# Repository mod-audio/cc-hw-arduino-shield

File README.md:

control-chain-arduino-shield
============================

This repository contains the schematics and PCB design files for Control Chain Arduino Shield hardware. It serves as a way for people to create new peripheral to be used in conjunction with MOD (http://moddevices.com/) via its Control Chain interface.

These files were created and can be improved with KiCAD, a free software Electronics CAD which is available at http://www.kicad.org/

## Check out instructions ##

This project uses a set of KiCAD symbols and footprints provided by the official KiCad library (https://github.com/KiCad/). In order to properly fetch these dependencies, which are configured as submodule repositories, you have to use the **--recursive** attribute in the following **git** command:

> git clone --recursive https://github.com/portalmod/control-chain-arduino-shield.git

## Licensing ##

This is an Open Hardware project and all of the files in this repository are licensed under the terms of the "Creative Commons By-SA" license.

## Sample Code / Arduino Library ##

There is an Arduino library for making it easy to develop your own Control Chain peripherals freely available at https://github.com/portalmod/control-chain-arduino-lib

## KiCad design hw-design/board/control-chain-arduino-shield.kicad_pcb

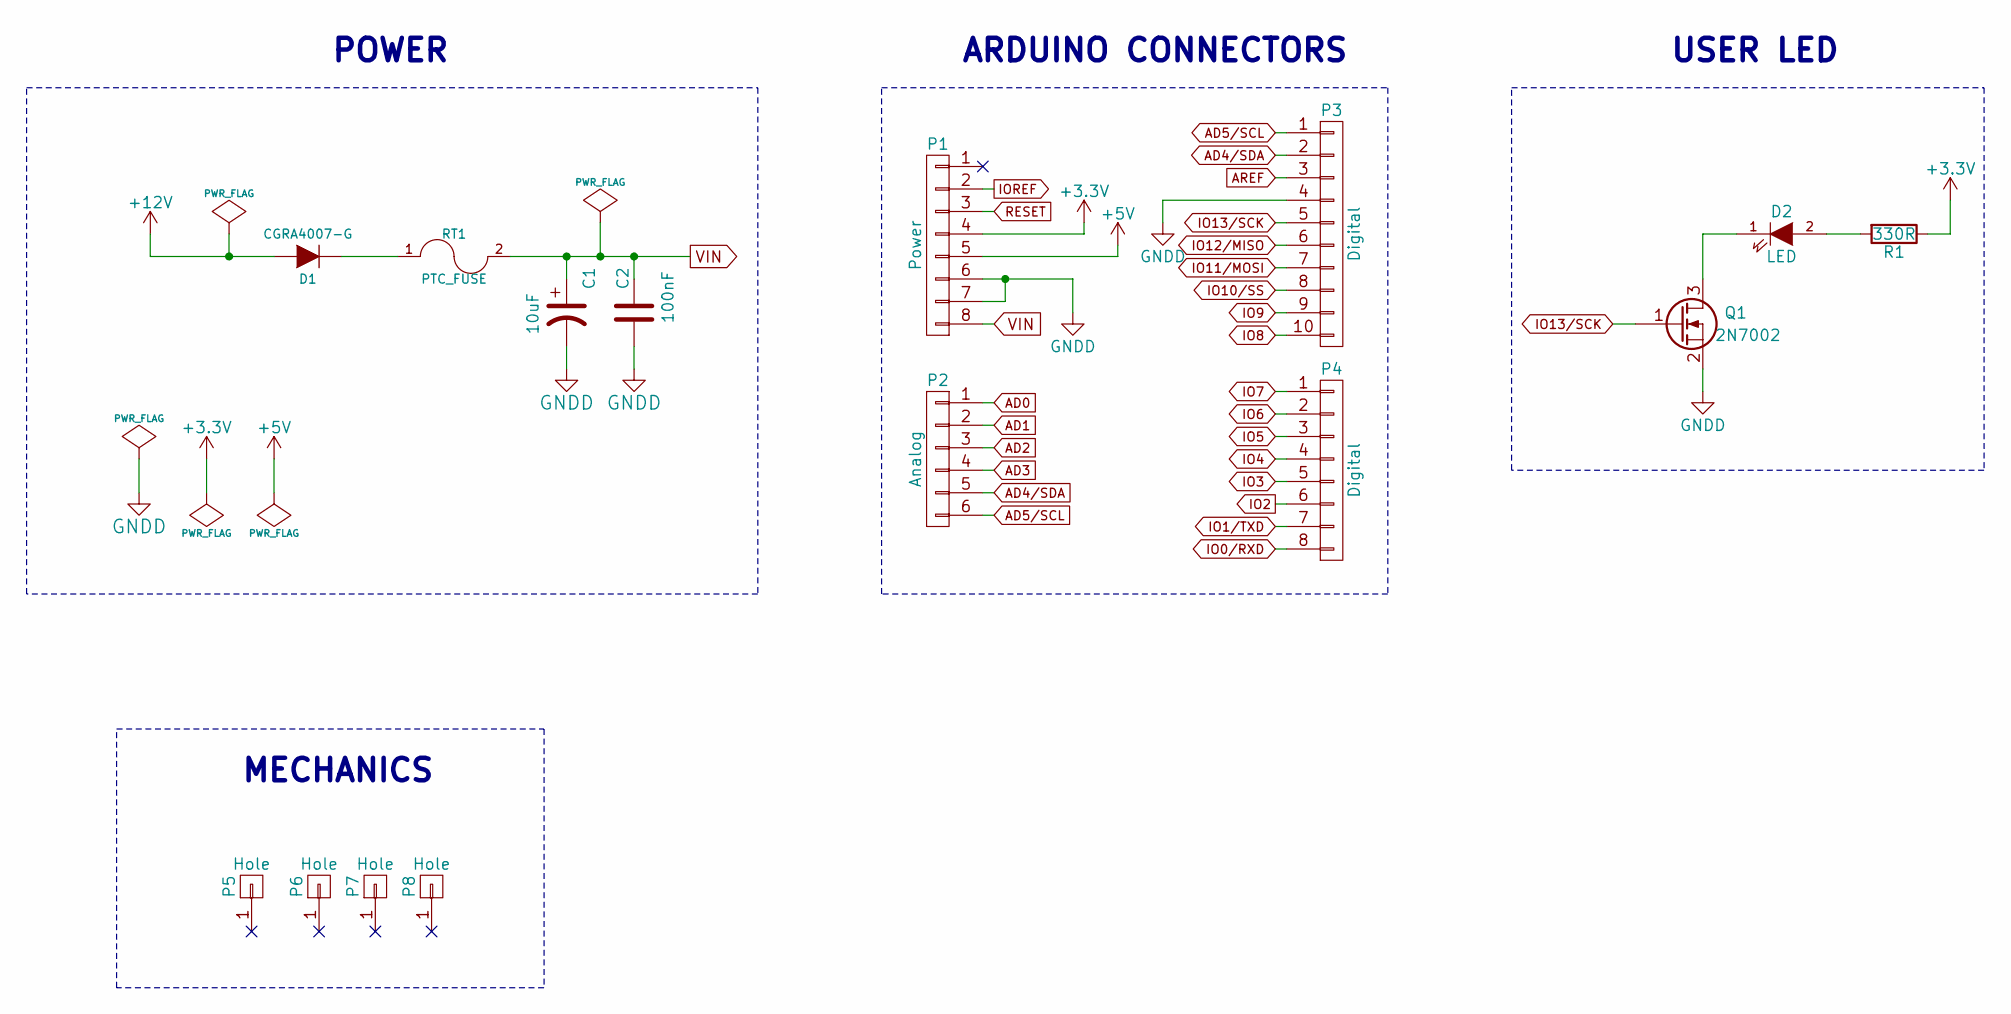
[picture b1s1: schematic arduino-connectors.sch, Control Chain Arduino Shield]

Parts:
C1: 10uF; c_elec_5x5.3; MPN UWX1E100MCL1GB
C2: 100nF; C_0603; MPN C1608X7R1E104K080AA
D1: CGRA4007-G; Diode-SMA_Standard; MPN CGRA4007-G
D2: LED; LED-0603; MPN LS Q976-NR-1
P1: Power; Socket_Strip_Arduino_1x08; MPN PREC008SFAN-RC
P2: Analog; Socket_Strip_Arduino_1x06; MPN PREC006SFAN-RC
P3: Digital; Socket_Strip_Arduino_1x10; MPN PREC010SFAN-RC
P4: Digital; Socket_Strip_Arduino_1x08; MPN PREC008SFAN-RC
P5, P6, P7, P8: Hole; Arduino_1pin
Q1: 2N7002; SOT-23; MPN 2N7002P,215
R1: 330R; R_0603; MPN RMCF0603JT330R
RT1: PTC_FUSE; R_1210; MPN 0ZCB0050FF2G

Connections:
+3V3: P1.4, R1.1; also elsewhere on the board
+5V: P1.5; also elsewhere on the board
+12V: D1.2 (A); also elsewhere on the board
AD0: P2.1; also elsewhere on the board
AD1: P2.2; also elsewhere on the board
AD2: P2.3; also elsewhere on the board
AD3: P2.4; also elsewhere on the board
AD4/SDA: P2.5, P3.2; also elsewhere on the board
AD5/SCL: P2.6, P3.1; also elsewhere on the board
AREF: P3.3; also elsewhere on the board
GNDD: C1.2, C2.2, P1.6, P1.7, P3.4, Q1.2 (S); also elsewhere on the board
IO0/RXD: P4.8; also elsewhere on the board
IO1/TXD: P4.7; also elsewhere on the board
IO2: P4.6; also elsewhere on the board
IO3: P4.5; also elsewhere on the board
IO4: P4.4; also elsewhere on the board
IO5: P4.3; also elsewhere on the board
IO6: P4.2; also elsewhere on the board
IO7: P4.1; also elsewhere on the board
IO8: P3.10; also elsewhere on the board
IO9: P3.9; also elsewhere on the board
IO10/SS: P3.8; also elsewhere on the board
IO11/MOSI: P3.7; also elsewhere on the board
IO12/MISO: P3.6; also elsewhere on the board
IO13/SCK: P3.5, Q1.1 (G); also elsewhere on the board
IOREF: P1.2; also elsewhere on the board
unnamed: D1.1 (K), RT1.1
unnamed: D2.1 (K), Q1.3 (D)
unnamed: D2.2 (A), R1.2
RESET: P1.3; also elsewhere on the board
VIN: C1.1, C2.1, P1.8, RT1.2; also elsewhere on the board

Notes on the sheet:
POWER
ARDUINO CONNECTORS
USER LED
MECHANICS

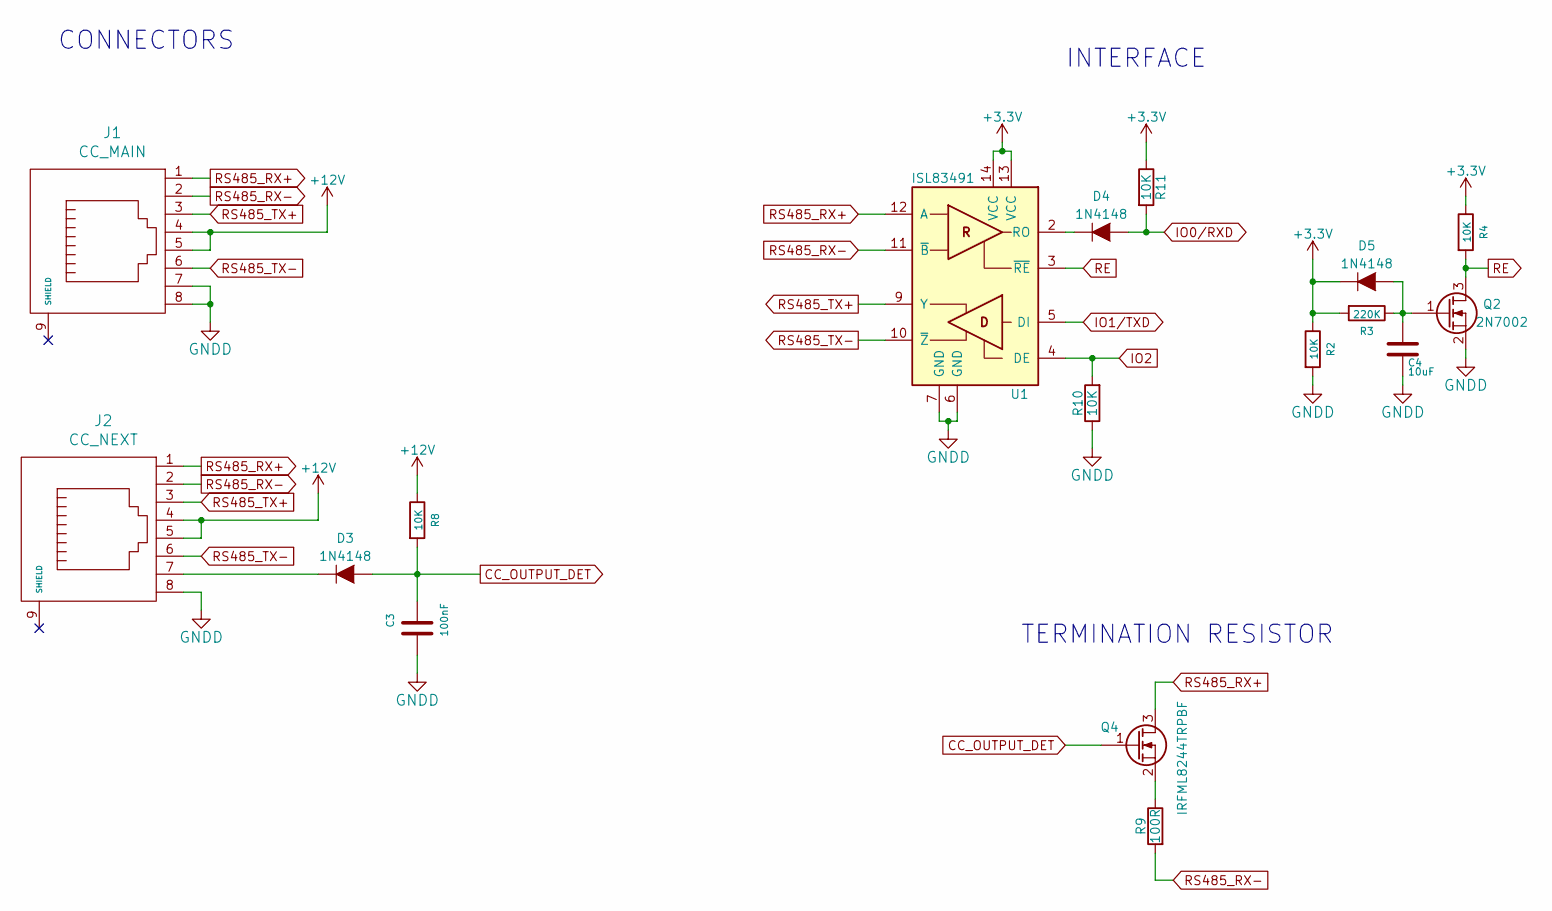
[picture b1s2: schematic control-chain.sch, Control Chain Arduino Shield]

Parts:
C3: 100nF; C_0603; MPN C1608X7R1E104K080AA
C4: 10uF; C_0603; MPN GRM188R60G106ME47D
D3, D4, D5: 1N4148; SOD-323; MPN 1N4148WX-TP
J1: CC_MAIN; 54602-908LF; MPN 54602-908LF
J2: CC_NEXT; 54602-908LF; MPN 54602-908LF
Q2: 2N7002; SOT-23; MPN 2N7002P,215
Q4: IRFML8244TRPBF; SOT-23; MPN IRFML8244TRPBF
R2, R4, R8, R10, R11: 10K; R_0603; MPN RMCF0603JT10K0
R3: 220K; R_0603; MPN RMCF0603JT220K
R9: 100R; R_0805; MPN ERJ-P06F1000V
U1: ISL83491; SOIC-14_3.9x8.7mm_Pitch1.27mm; MPN ISL83491IBZ

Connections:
+3V3: D5.1 (K), R2.1, R3.2, R4.1, R11.1, U1.13 (VCC), U1.14 (VCC); also elsewhere on the board
+12V: J1.4, J1.5, J2.4, J2.5, R8.1; also elsewhere on the board
CC_OUTPUT_DET: C3.1, D3.2 (A), Q4.1 (G), R8.2
GNDD: C3.2, C4.2, J1.7, J1.8, J2.8, Q2.2 (S), R2.2, R10.1, U1.6 (GND), U1.7 (GND); also elsewhere on the board
IO0/RXD: D4.2 (A), R11.2; also elsewhere on the board
IO1/TXD: U1.5 (DI); also elsewhere on the board
IO2: R10.2, U1.4 (DE); also elsewhere on the board
unnamed: C4.1, D5.2 (A), Q2.1 (G), R3.1
unnamed: D3.1 (K), J2.7
unnamed: D4.1 (K), U1.2 (RO)
unnamed: Q4.2 (S), R9.1
RE: Q2.3 (D), R4.2, U1.3 (~RE)
RS485_RX+: J1.1, J2.1, Q4.3 (D), U1.12 (A)
RS485_RX-: J1.2, J2.2, R9.2, U1.11 (~B)
RS485_TX+: J1.3, J2.3, U1.9 (Y)
RS485_TX-: J1.6, J2.6, U1.10 (~Z~)

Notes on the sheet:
TERMINATION RESISTOR
CONNECTORS
INTERFACE

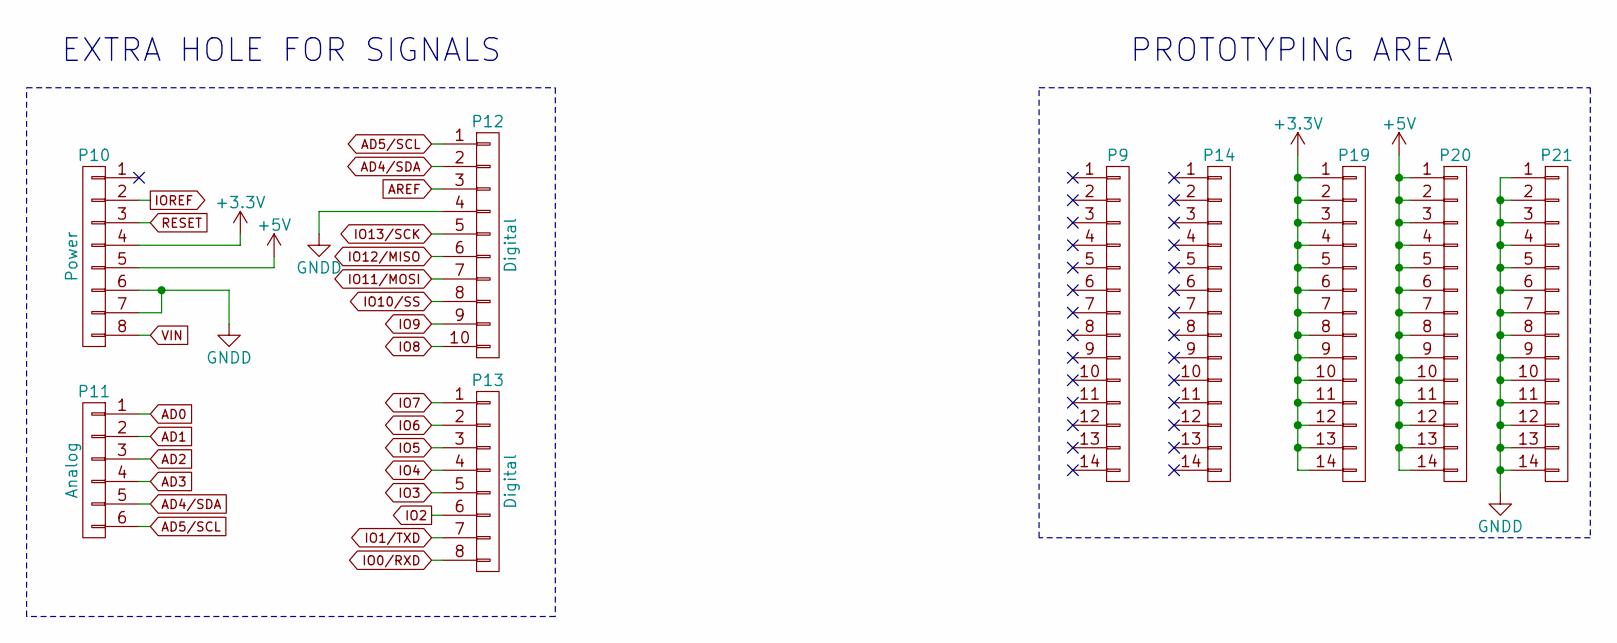
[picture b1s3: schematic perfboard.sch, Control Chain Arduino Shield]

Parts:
P9, P14: Perfboard
P10: Power; Socket_Strip_Arduino_1x08
P11: Analog; Socket_Strip_Arduino_1x06
P12: Digital; Socket_Strip_Arduino_1x10
P13: Digital; Socket_Strip_Arduino_1x08
P19, P20, P21: Pin_Header_Straight_1x14

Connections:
+3V3: P10.4, P19.1, P19.2, P19.3, P19.4, P19.5, P19.6, P19.7, P19.8, P19.9, P19.10, P19.11, P19.12, P19.13, P19.14; also elsewhere on the board
+5V: P10.5, P20.1, P20.2, P20.3, P20.4, P20.5, P20.6, P20.7, P20.8, P20.9, P20.10, P20.11, P20.12, P20.13, P20.14; also elsewhere on the board
AD0: P11.1; also elsewhere on the board
AD1: P11.2; also elsewhere on the board
AD2: P11.3; also elsewhere on the board
AD3: P11.4; also elsewhere on the board
AD4/SDA: P11.5, P12.2; also elsewhere on the board
AD5/SCL: P11.6, P12.1; also elsewhere on the board
AREF: P12.3; also elsewhere on the board
GNDD: P10.6, P10.7, P12.4, P21.1, P21.2, P21.3, P21.4, P21.5, P21.6, P21.7, P21.8, P21.9, P21.10, P21.11, P21.12, P21.13, P21.14; also elsewhere on the board
IO0/RXD: P13.8; also elsewhere on the board
IO1/TXD: P13.7; also elsewhere on the board
IO2: P13.6; also elsewhere on the board
IO3: P13.5; also elsewhere on the board
IO4: P13.4; also elsewhere on the board
IO5: P13.3; also elsewhere on the board
IO6: P13.2; also elsewhere on the board
IO7: P13.1; also elsewhere on the board
IO8: P12.10; also elsewhere on the board
IO9: P12.9; also elsewhere on the board
IO10/SS: P12.8; also elsewhere on the board
IO11/MOSI: P12.7; also elsewhere on the board
IO12/MISO: P12.6; also elsewhere on the board
IO13/SCK: P12.5; also elsewhere on the board
IOREF: P10.2; also elsewhere on the board
RESET: P10.3; also elsewhere on the board
VIN: P10.8; also elsewhere on the board

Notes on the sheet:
EXTRA HOLE FOR SIGNALS
PROTOTYPING AREA

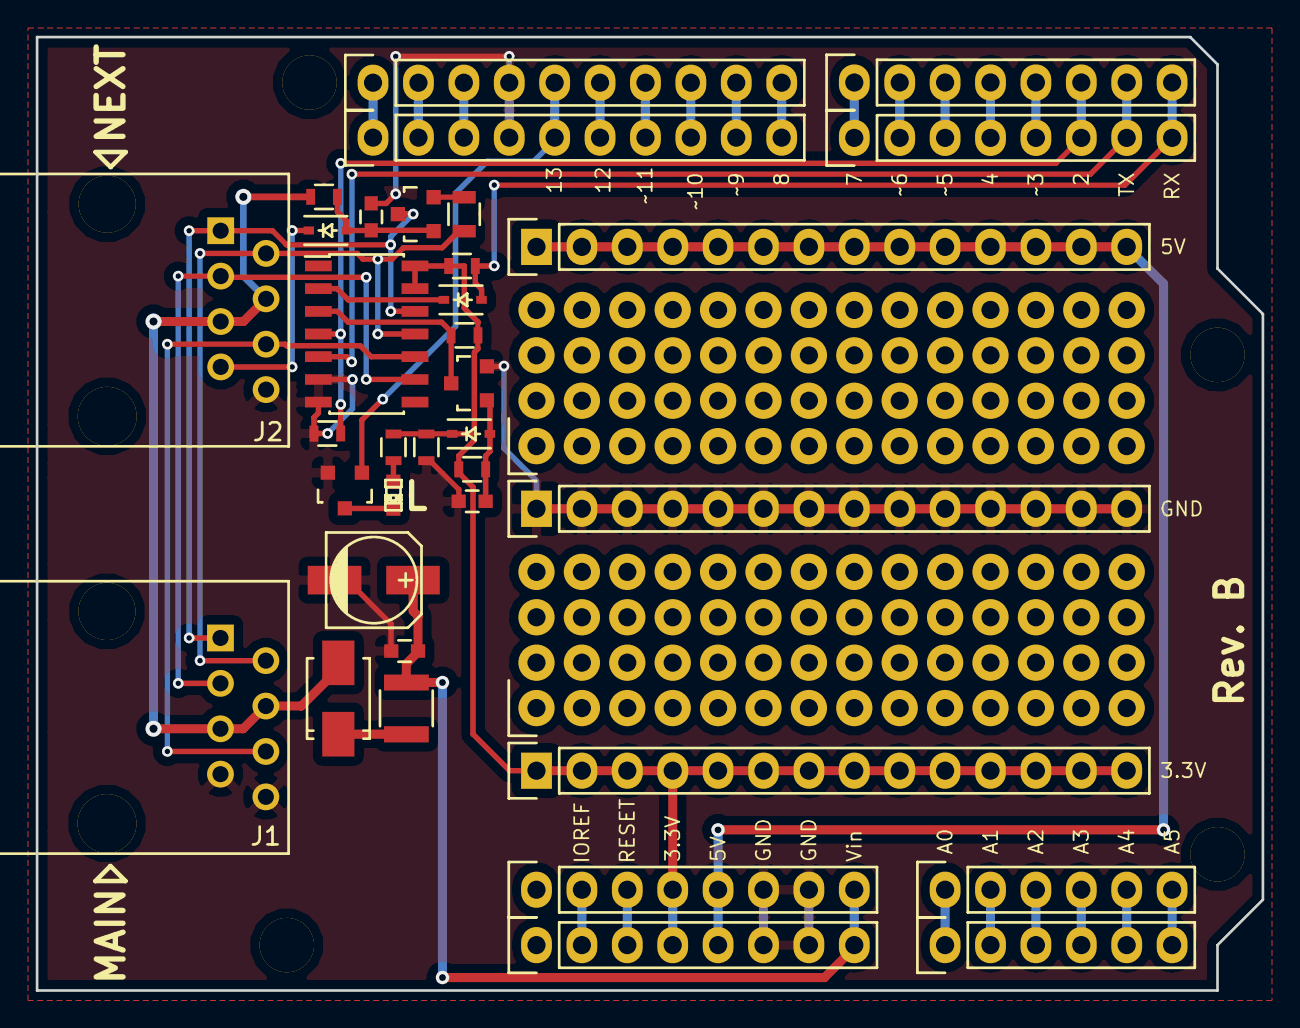
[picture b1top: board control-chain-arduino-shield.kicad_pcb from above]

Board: 2 copper layers, 68.6 x 53.3 mm, 41 parts (0 on the bottom side), 41 nets.

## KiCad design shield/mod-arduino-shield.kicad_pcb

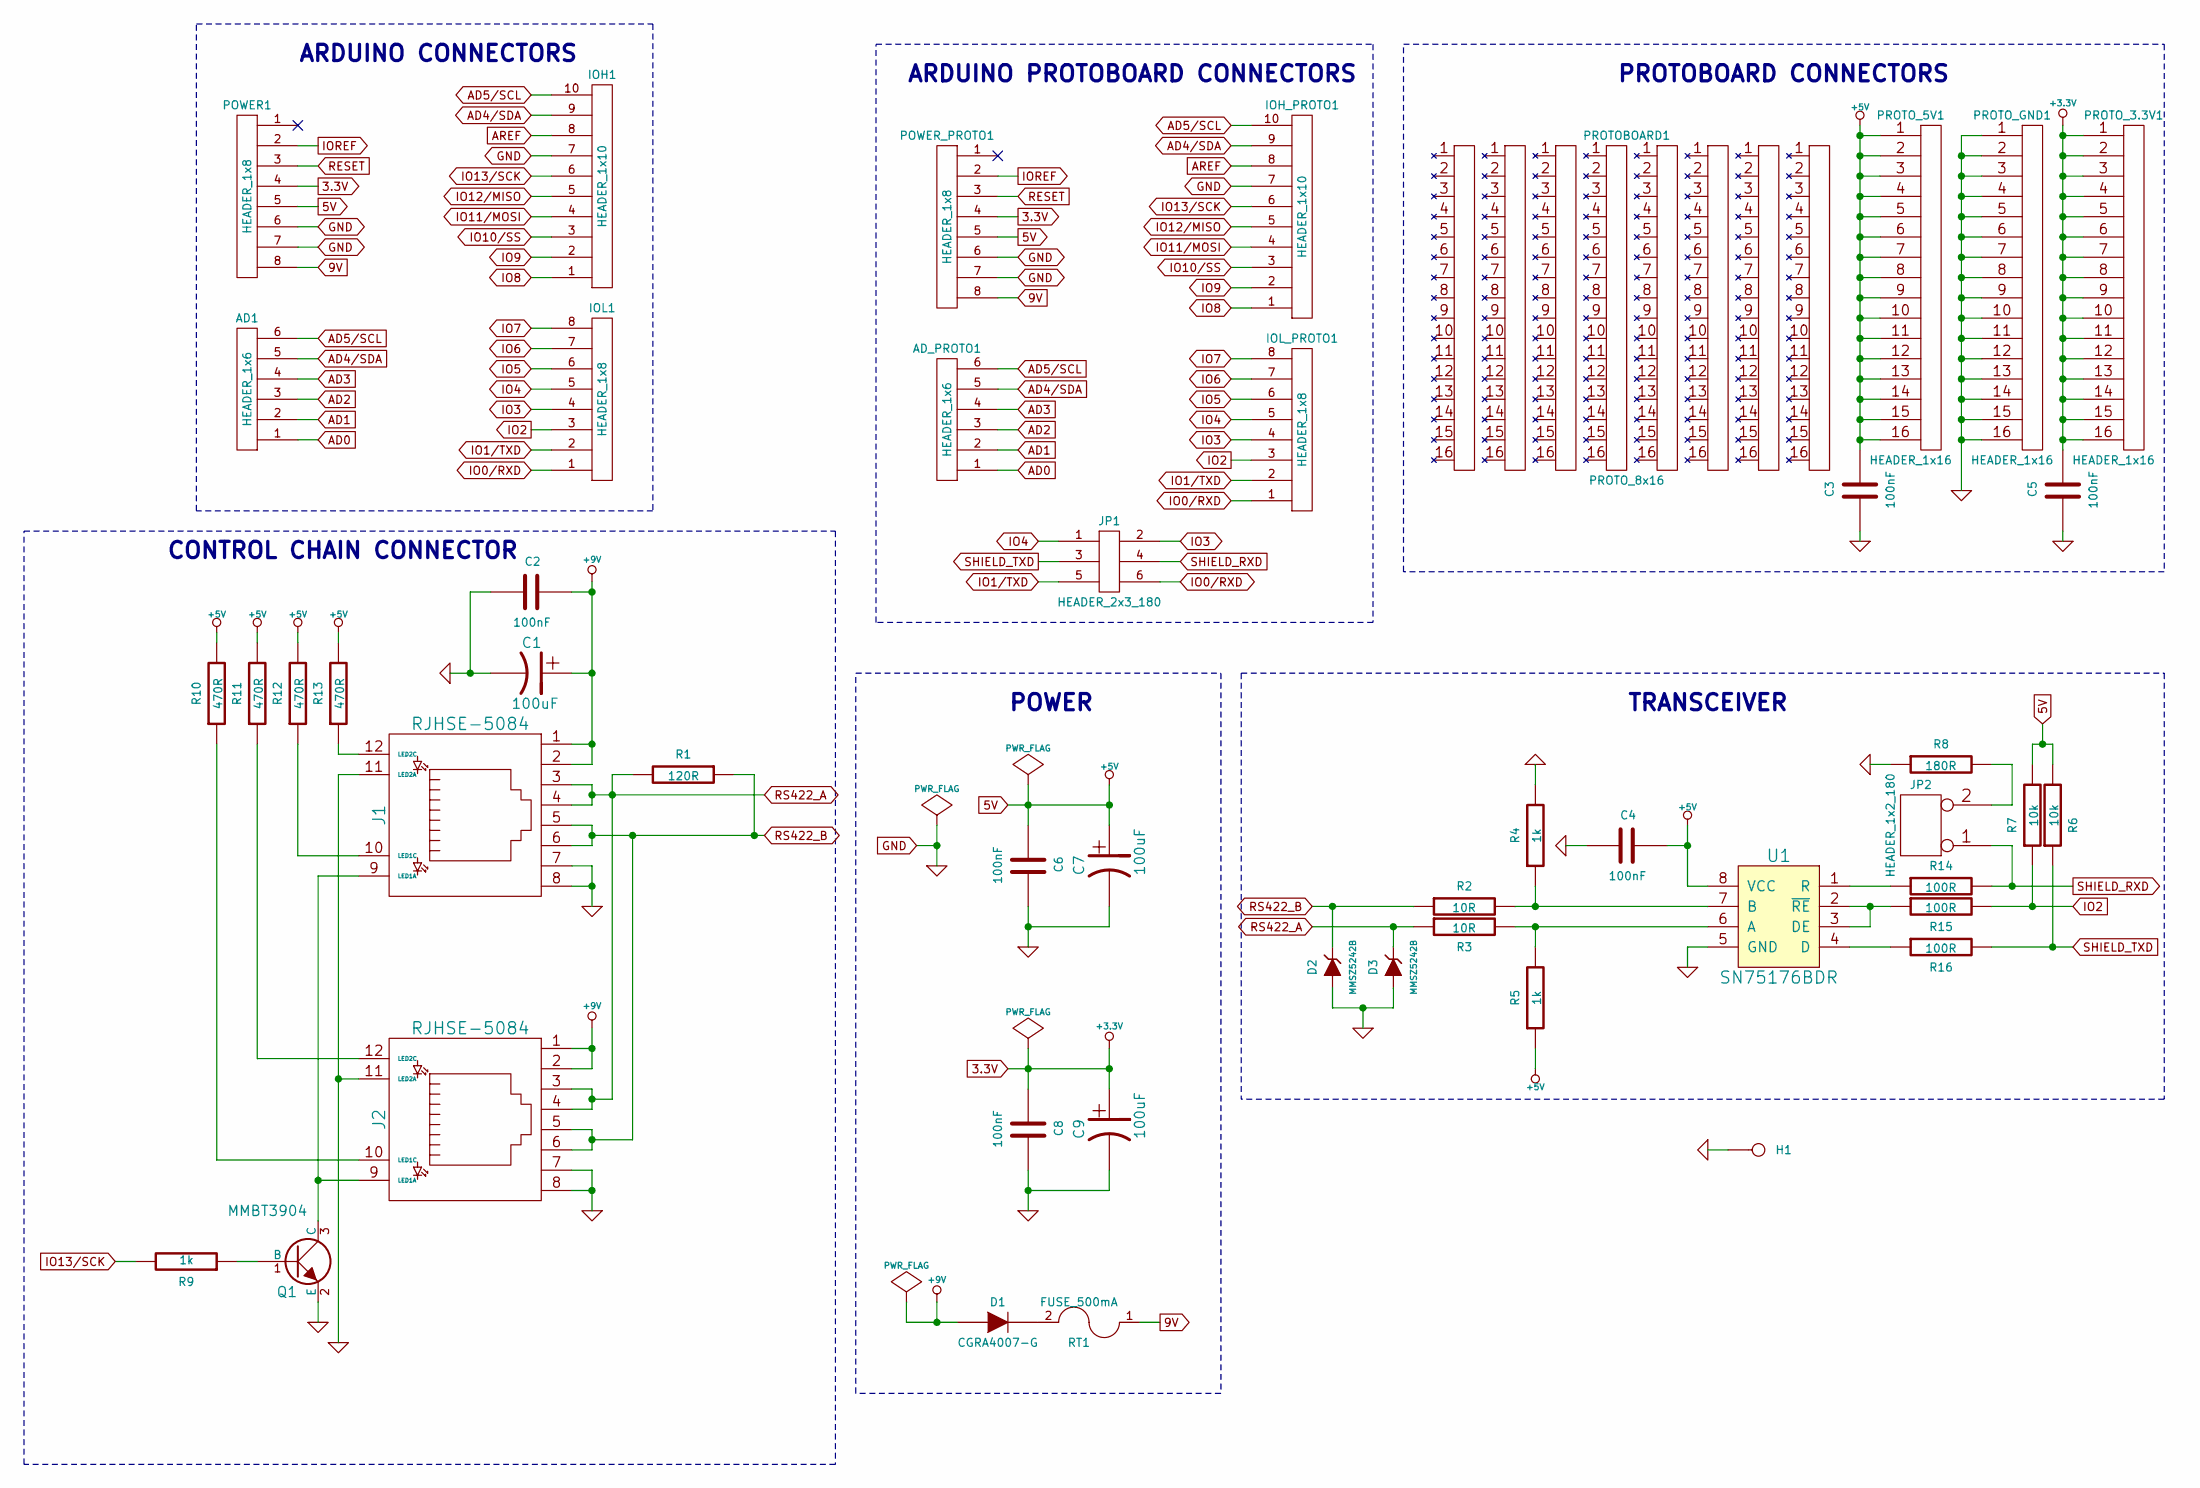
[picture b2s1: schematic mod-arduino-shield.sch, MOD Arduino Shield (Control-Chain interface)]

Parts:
AD1: HEADER_1x6; HEADER_100MIL_1R6P_PTH
AD_PROTO1: HEADER_1x6; HEADER_100MIL_1R6P_PTH
C1, C7, C9: 100uF; CAP_RAD_5MM
C2, C3, C4, C5, C6, C8: 100nF; SM0805
D1: CGRA4007-G; DO-214AC(SMA)
D2, D3: MMSZ5242B; SOD123
H1: HOLE; HOLE_3MM
IOH1: HEADER_1x10; HEADER_100MIL_1R10P_PTH
IOH_PROTO1: HEADER_1x10; HEADER_100MIL_1R10P_PTH
IOL1: HEADER_1x8; HEADER_100MIL_1R8P_PTH
IOL_PROTO1: HEADER_1x8; HEADER_100MIL_1R8P_PTH
J1, J2: RJHSE-5084; RJ45-RJHSE5084
JP1: HEADER_2x3_180; HEADER_100MIL_2R3P_PTH
JP2: HEADER_1x2_180; HEADER_100MIL_1R2P_PTH
POWER1: HEADER_1x8; HEADER_100MIL_1R8P_PTH
POWER_PROTO1: HEADER_1x8; HEADER_100MIL_1R8P_PTH
PROTOBOARD1: PROTO_8x16; PROTOBOARD_100MIL_8R16P_PTH
PROTO_3.3V1, PROTO_5V1: HEADER_1x16; PROTOBOARD_100MIL_1R16P_PTH
PROTO_GND1: HEADER_1x16; PROTOBOARD_100MIL_1R16P_PTH
Q1: MMBT3904; SOT23
R1: 120R; SM0805
R2, R3: 10R; SM0805
R4, R5, R9: 1k; SM0805
R6, R7: 10k; SM0805
R8: 180R; SM0805
R10, R11, R12, R13: 470R; SM0805
R14, R15, R16: 100R; SM0805
RT1: FUSE_500mA; SM1210
U1: SN75176BDR; SO8E

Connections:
3.3V: C5.2, C8.2, C9.1, POWER1.4, POWER_PROTO1.4, PROTO_3.3V1.1, PROTO_3.3V1.2, PROTO_3.3V1.3, PROTO_3.3V1.4, PROTO_3.3V1.5, PROTO_3.3V1.6, PROTO_3.3V1.7, PROTO_3.3V1.8, PROTO_3.3V1.9, PROTO_3.3V1.10, PROTO_3.3V1.11, PROTO_3.3V1.12, PROTO_3.3V1.13, PROTO_3.3V1.14, PROTO_3.3V1.15, PROTO_3.3V1.16
5V: C3.2, C4.2, C6.2, C7.1, POWER1.5, POWER_PROTO1.5, PROTO_5V1.1, PROTO_5V1.2, PROTO_5V1.3, PROTO_5V1.4, PROTO_5V1.5, PROTO_5V1.6, PROTO_5V1.7, PROTO_5V1.8, PROTO_5V1.9, PROTO_5V1.10, PROTO_5V1.11, PROTO_5V1.12, PROTO_5V1.13, PROTO_5V1.14, PROTO_5V1.15, PROTO_5V1.16, R5.1, R6.2, R7.2, R10.2, R11.2, R12.2, R13.2, U1.8 (VCC)
9V: POWER1.8, POWER_PROTO1.8, RT1.1
+9V: C1.1, C2.2, D1.1 (A), J1.1, J1.2, J2.1, J2.2
AD0: AD1.1, AD_PROTO1.1
AD1: AD1.2, AD_PROTO1.2
AD2: AD1.3, AD_PROTO1.3
AD3: AD1.4, AD_PROTO1.4
AD4/SDA: AD1.5, AD_PROTO1.5, IOH1.9, IOH_PROTO1.9
AD5/SCL: AD1.6, AD_PROTO1.6, IOH1.10, IOH_PROTO1.10
AREF: IOH1.8, IOH_PROTO1.8
GND: C1.2, C2.1, C3.1, C4.1, C5.1, C6.1, C7.2, C8.1, C9.2, D2.1 (A), D3.1 (A), H1.1, IOH1.7, IOH_PROTO1.7, J1.7, J1.8, J1.11 (LED2A), J2.7, J2.8, J2.11 (LED2A), POWER1.6, POWER1.7, POWER_PROTO1.6, POWER_PROTO1.7, PROTO_GND1.1, PROTO_GND1.2, PROTO_GND1.3, PROTO_GND1.4, PROTO_GND1.5, PROTO_GND1.6, PROTO_GND1.7, PROTO_GND1.8, PROTO_GND1.9, PROTO_GND1.10, PROTO_GND1.11, PROTO_GND1.12, PROTO_GND1.13, PROTO_GND1.14, PROTO_GND1.15, PROTO_GND1.16, Q1.2 (E), R4.2, R8.1, U1.5 (GND)
IO0/RXD: IOL1.1, IOL_PROTO1.1, JP1.6
IO1/TXD: IOL1.2, IOL_PROTO1.2, JP1.5
IO2: IOL1.3, IOL_PROTO1.3, R7.1, R15.2
IO3: IOL1.4, IOL_PROTO1.4, JP1.2 (P1)
IO4: IOL1.5, IOL_PROTO1.5, JP1.1
IO5: IOL1.6, IOL_PROTO1.6
IO6: IOL1.7, IOL_PROTO1.7
IO7: IOL1.8, IOL_PROTO1.8
IO8: IOH1.1, IOH_PROTO1.1
IO9: IOH1.2, IOH_PROTO1.2
IO10/SS: IOH1.3, IOH_PROTO1.3
IO11/MOSI: IOH1.4, IOH_PROTO1.4
IO12/MISO: IOH1.5, IOH_PROTO1.5
IO13/SCK: IOH1.6, IOH_PROTO1.6, R9.2
IOREF: POWER1.2, POWER_PROTO1.2
unnamed: D1.2 (K), RT1.2
unnamed: J1.9 (LED1A), J2.9 (LED1A), Q1.3 (C)
unnamed: J1.10 (LED1C), R12.1
unnamed: J1.12 (LED2C), R13.1
unnamed: J2.10 (LED1C), R10.1
unnamed: J2.12 (LED2C), R11.1
unnamed: JP2.2 (PM), R8.2
unnamed: Q1.1 (B), R9.1
unnamed: R2.2, R4.1, U1.7 (B)
unnamed: R3.2, R5.2, U1.6 (A)
unnamed: R14.1, U1.1 (R)
unnamed: R15.1, U1.2 (~RE), U1.3 (DE)
unnamed: R16.1, U1.4 (D)
RESET: POWER1.3, POWER_PROTO1.3
RS422_A: D3.2 (K), J1.3, J1.4, J2.3, J2.4, R1.2, R3.1
RS422_B: D2.2 (K), J1.5, J1.6, J2.5, J2.6, R1.1, R2.1
SHIELD_RXD: JP1.4 (P2), JP2.1, R14.2
SHIELD_TXD: JP1.3 (P2), R6.1, R16.2

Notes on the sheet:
CONTROL CHAIN CONNECTOR
ARDUINO CONNECTORS
ARDUINO PROTOBOARD CONNECTORS
PROTOBOARD CONNECTORS
TRANSCEIVER
POWER

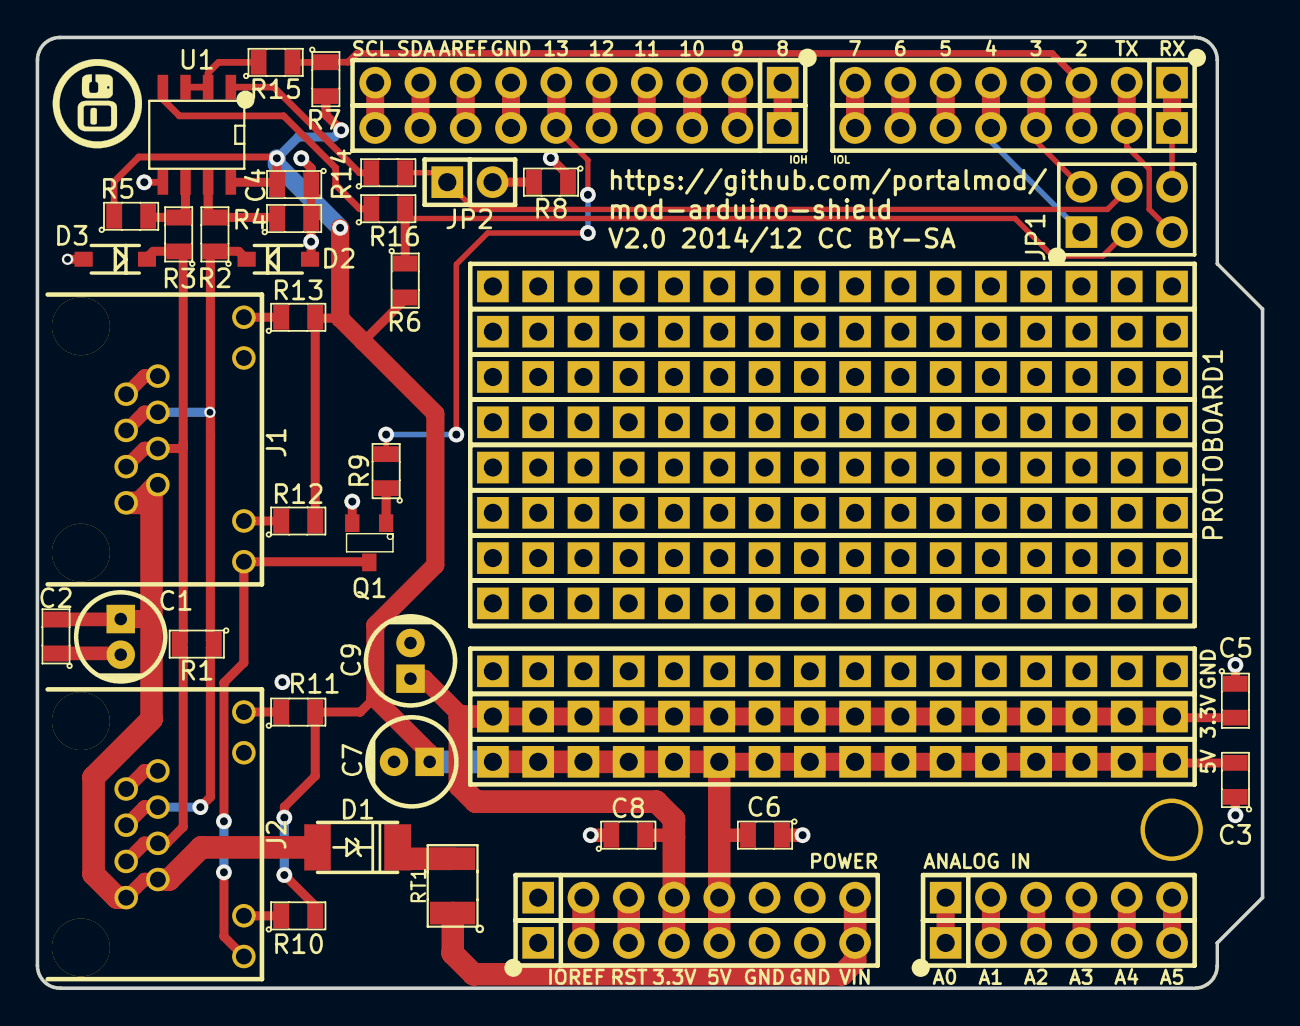
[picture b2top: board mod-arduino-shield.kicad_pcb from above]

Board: 2 copper layers, 68.7 x 53.3 mm, 49 parts (0 on the bottom side), 45 nets.

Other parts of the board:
LOGO: LOGO; MOD_Logo_Small

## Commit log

2014-09-16 Initial commit for MOD Arduino Shield. Shield for interfacing the Arduino to the Control Chain of MOD. Opening the hardware for the community.
2014-12-01 Improving README.md and declaring the copyright license for this repository.
2014-12-02 Adding a few footprints exported from the footswitch repository that were using the old library file format (.mod).
2014-12-02 replacing specific references and values in the footprints by generic ones
2014-12-04 Fixing typo in the .gitignore filename and actually deleting the files it should be ignoring.
2014-12-04 Adding metadata to the schematics of the example circuits.
2014-12-04 removing local copy of footprints and adding the mod-kicad-footprints repository as a submodule dependency
2014-12-04 updating component => footprint mapping file to use the new footprint library
2014-12-04 improving the README and pointing users to the repository containing sample code and the arduino library (fix issue #5)
2014-12-04 add metadata and licensing info to the schematics file (fix issue #4)
2014-12-09 fix issue #3: Add "CC by-SA" license logo to the PCB silk layer Added MOD logo and improved/rearranged previous silk text.
2014-12-09 fix issue #6: use same labels on shield as used in arduino
2014-12-09 fix issue #2: rename VCCIO to IOREF
2014-12-09 fix issue #1: IOREF should not be used to power the circuit
2014-12-18 plotting the schematics to PDF files to be kept in the /docs directories (we should always update these PDF files when we make changes to the schematics).
2015-06-25 README updated
2015-06-25 added hw-design directory
2015-06-25 sch: setting up footprints
2015-06-26 adding footprint to local project directory (submodule)
2015-06-26 BOM generated
2015-06-26 importing arduino uno layout template
2015-06-26 sch: fixing footprints and renaming some connectors
2015-06-26 pcb: importing netlist
2015-06-26 pcb: RJ45 connectors placed
2015-06-26 sch: adjusting perfboard
2015-06-26 pcb: initial placement of components
2015-06-26 pcb: setting design rules
2015-06-26 pcb: design almost done, missing 2 or 3 tracks
2015-06-29 sch: fixing connectors I/Os pinout
2015-06-29 pcb: all tracks done + silkscreen of I/Os
2015-06-29 pcb: adjusting holes
2015-06-29 BOM updated
2015-06-29 removing old stuff
2015-09-29 sch: changing input voltage from +9V to +12V
2015-10-15 sch: fixing MOSFET + new BOM exported
2015-10-15 pcb: updating layout
2015-10-17 adding board size
2015-10-17 improving silkscreen
2015-10-17 panel created
2015-10-17 fixing user led voltage
2016-06-08 fix RJ45 pinout
2016-06-08 fix all DRC issues
2016-06-08 add perfboard footprint
2016-06-08 replace multiple headers by perfboard
2016-06-08 fix pin name (vin)
2016-06-08 new netlist
2016-06-09 connect all voltage inputs pins
2016-06-09 update layout to last schematic
2016-06-17 change RJ45 connector
2016-06-17 add header MPN to BOM
2016-06-17 add local footprint library
2016-07-12 remove panel gerber files
2016-07-12 update BOM
2016-07-12 export gerber
2016-07-12 remove panel project files
2017-04-26 generate schematic pdf
2018-05-18 add enable circuit for RE pin
2018-05-18 update footprints (remove silkscreen from pads)
2018-05-18 move led position
2018-05-18 update gerber and pdf files
2021-11-10 Update README.md
    https://forum.kicad.info/t/warning-avoid-all-links-to-kicad-pcb-org-use-kicad-org/31521

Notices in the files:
shield/mod-arduino-shield.kicad_pcb:
V2.0 2014/12 CC BY-SA
shield/mod-arduino-shield.sch:
Licensed under Creative Commons By SA
